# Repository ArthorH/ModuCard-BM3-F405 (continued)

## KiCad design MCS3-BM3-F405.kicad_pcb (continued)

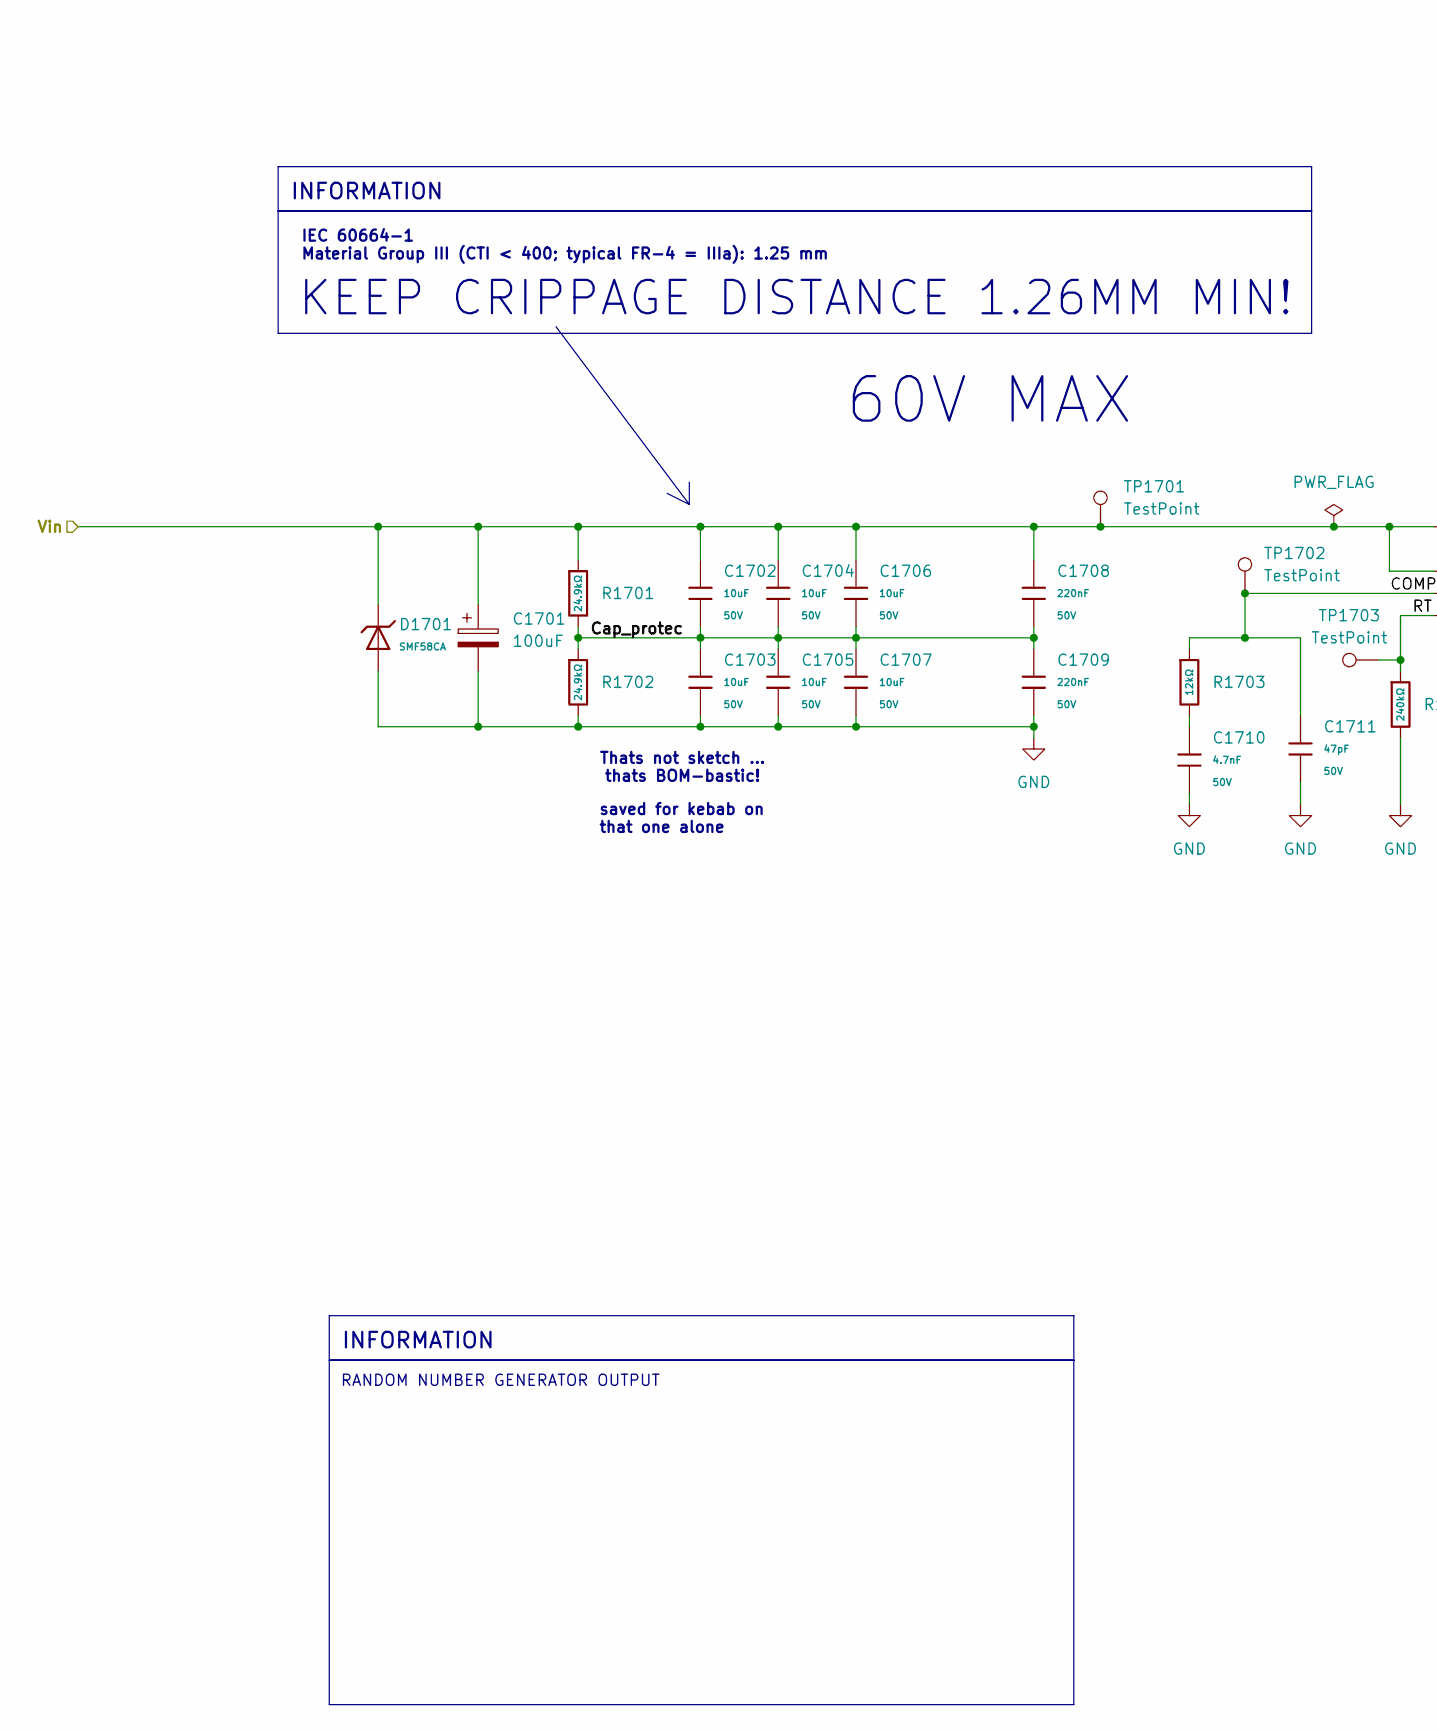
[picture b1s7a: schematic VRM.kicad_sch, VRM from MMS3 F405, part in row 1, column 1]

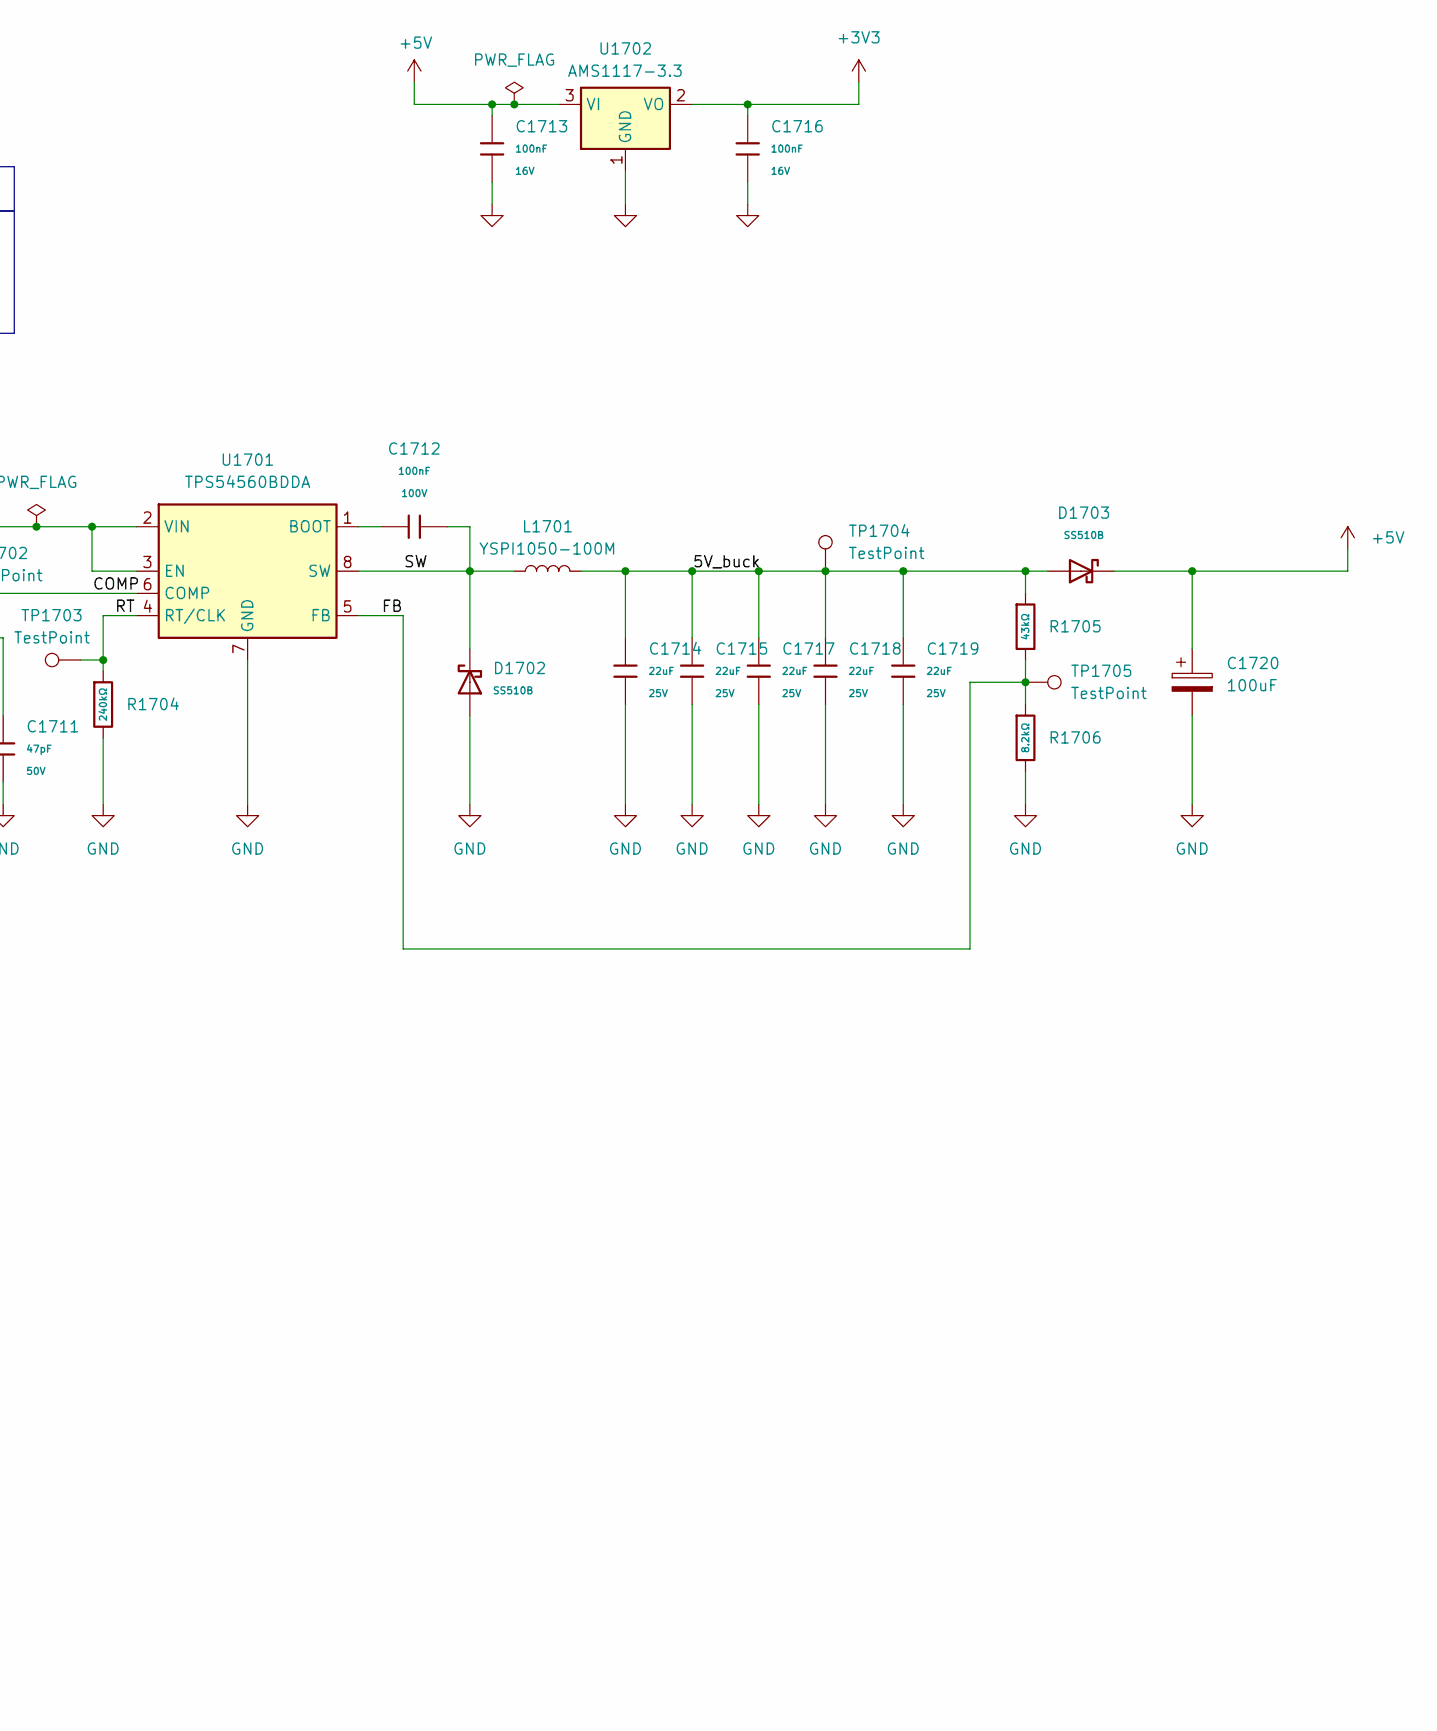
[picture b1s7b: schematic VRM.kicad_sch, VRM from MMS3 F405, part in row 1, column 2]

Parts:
C1701, C1720: 100uF; CP_Elec_10x10; MPN VZH101M1KTR-1010; LCSC C249838
C1702, C1703, C1704, C1705, C1706, C1707: 10uF; C_0805; Voltage Rated 50V; Tolerance ±10%; Part GRM21BR61H106KE43L; LCSC C440198
C1708, C1709: 220nF; C_0805; Voltage Rated 50V; Tolerance ±10%; Part CL21B224KBFNNNE; LCSC C5378
C1710: 4.7nF; C_0402; Voltage Rated 50V; Tolerance ±10%; Part 0402B472K500NT; LCSC C1538
C1711: 47pF; C_0402; Voltage Rated 50V; Tolerance ±5%; Part 0402CG470J500NT; LCSC C1567
C1712: 100nF; C_0805; Voltage Rated 100V; Tolerance ±10%; Part CL21B104KCFNNNE; LCSC C28233
C1713, C1716: 100nF; C_0402; Voltage Rated 16V; Tolerance ±10%; Part CL05B104KO5NNNC; LCSC C1525
C1714, C1715, C1717, C1718, C1719: 22uF; C_0805; Voltage Rated 25V; Tolerance ±20%; Part CL21A226MAQNNNE; LCSC C45783
D1701: SMF58CA; D_SOD-123FL; Clamping Voltage 93.6V; Voltage - Breakdown 71.2V; Part SMF58CA; LCSC C42371753
D1702, D1703: SS510B; D_SMB; Forward Voltage (Vf@If) 0.85V@5.0A; Reverse Voltage (Vr) 100V; Part SS510B; LCSC C7420368
L1701: YSPI1050-100M; L_Sunlord_MWSA1005S; LCSC C497897
R1701, R1702: 24.9kΩ; R_0402; Overload Voltage (Max) 50V; Tolerance ±1%; Part 0402WGF2402TCE; LCSC C25874
R1703: 12kΩ; R_0402; Overload Voltage (Max) 50V; Tolerance ±1%; Part 0402WGF1202TCE; LCSC C25752
R1704: 240kΩ; R_0603; Overload Voltage (Max) 75V; Tolerance ±1%; Part 0603WAF2403T5E; LCSC C4197
R1705: 43kΩ; R_0603; Overload Voltage (Max) 75V; Tolerance ±1%; Part 0603WAF4302T5E; LCSC C23172
R1706: 8.2kΩ; R_0402; Overload Voltage (Max) 50V; Tolerance ±1%; Part 0402WGF8201TCE; LCSC C25924
TP1701, TP1702, TP1703, TP1704, TP1705: TestPoint; TestPoint_Pad_D1.0mm
U1701: TPS54560BDDA; Texas_R-PDSO-G8_EP2.95x4.9mm_Mask2.4x3.1mm_ThermalVias
U1702: AMS1117-3.3; SOT-223-3_TabPin2

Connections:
+3V3: C1716.1, U1702.2 (VO); also elsewhere on the board
+5V: C1713.1, C1720.1, D1703.1, U1702.3 (VI); also elsewhere on the board
/VRM/5V_buck: C1714.1, C1715.1, C1717.1, C1718.1, C1719.1, D1703.2, L1701.2, R1705.1, TP1704.1 (1_1)
/VRM/COMP: C1711.1, R1703.1, TP1702.1 (1_1), U1701.6 (COMP)
/VRM/Cap_protec: C1702.2, C1703.1, C1704.2, C1705.1, C1706.2, C1707.1, C1708.2, C1709.1, R1701.2, R1702.1
/VRM/FB: R1705.2, R1706.1, TP1705.1 (1_1), U1701.5 (FB)
/VRM/RT: R1704.1, TP1703.1 (1_1), U1701.4 (RT/CLK)
/VRM/SW: C1712.1, D1702.1, L1701.1, U1701.8 (SW)
GND: C1701.2, C1703.2, C1705.2, C1707.2, C1709.2, C1710.2, C1711.2, C1713.2, C1714.2, C1715.2, C1716.2, C1717.2, C1718.2, C1719.2, C1720.2, D1701.2, D1702.2, R1702.2, R1704.2, R1706.2, U1701.7 (GND), U1701.9 (GND), U1702.1 (GND); also elsewhere on the board
unnamed: C1710.1, R1703.2
unnamed: C1712.2, U1701.1 (BOOT)
Vbat: C1701.1, C1702.1, C1704.1, C1706.1, C1708.1, D1701.1, R1701.1, TP1701.1 (1_1), U1701.2 (VIN), U1701.3 (EN); also elsewhere on the board

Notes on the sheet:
saved for kebab on that one alone
INFORMATION
KEEP CRIPPAGE DISTANCE 1.26MM MIN!
Thats not sketch ... thats BOM-bastic!
RANDOM NUMBER GENERATOR OUTPUT
60V MAX
IEC 60664-1 Material Group III (CTI < 400; typical FR-4 = IIIa): 1.25 mm

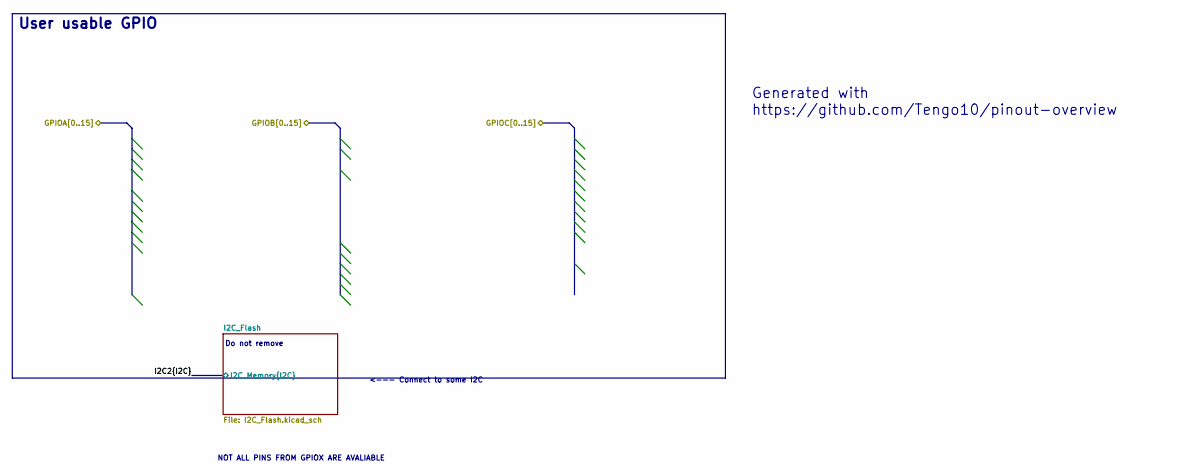
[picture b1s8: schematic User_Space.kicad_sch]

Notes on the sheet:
Do not remove
Generated with https://github.com/Tengo10/pinout-overview
<--- Connect to some I2C
User usable GPIO
NOT ALL PINS FROM GPIOX ARE AVALIABLE

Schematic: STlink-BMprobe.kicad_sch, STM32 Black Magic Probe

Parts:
C901, C905, C906, C907, C908, C909: 100nF; C_0402; Voltage Rated 50V; Tolerance ±10%; Part CL05B104KB54PNC; LCSC C307331
C902, C904: 33pF; C_0402; Voltage Rated 50V; Tolerance ±5%; Part 0402CG330J500NT; LCSC C1562
C903: 1uF; C_0402; Voltage Rated 25V; Tolerance ±10%; Part CL05A105KA5NQNC; LCSC C52923
D901, D902: Red; D_0603; Part KT-0603R; LCSC C2286
J901: Conn_02x02_Counter_Clockwise; PinSocket_2x02_P2.54mm_Vertical; not fitted
Q901: MMST3904; SOT-23; Part MMST3904; LCSC C20526
R901, R904: 100kΩ; R_0402; Overload Voltage (Max) 50V; Tolerance ±1%; Part 0402WGF1003TCE; LCSC C25741
R902, R903, R908, R909: 22Ω; R_0402; Overload Voltage (Max) 50V; Tolerance ±1%; Part 0402WGF220JTCE; LCSC C25092
R905, R917: 100Ω; R_0402; Overload Voltage (Max) 50V; Tolerance ±1%; Part 0402WGF1000TCE; LCSC C25076
R906, R912, R913, R915: 10kΩ; R_0402; Overload Voltage (Max) 50V; Tolerance ±1%; Part 0402WGF1002TCE; LCSC C25744
R907: 10kΩ; R_0402; Overload Voltage (Max) 50V; Tolerance ±1%; Part 0402WGF1002TCE; LCSC C25744; not fitted
R910, R911: 220Ω; R_0402; Overload Voltage (Max) 50V; Tolerance ±1%; Part 0402WGF2200TCE; LCSC C25091
R914: 1.5kΩ; R_0402; Overload Voltage (Max) 50V; Tolerance ±1%; Part 0402WGF1501TCE; LCSC C25867
R916: 24.9kΩ; R_0402; Overload Voltage (Max) 50V; Tolerance ±1%; Part 0402WGF2402TCE; LCSC C25874
TP901, TP902, TP903, TP904, TP905, TP906, TP907, TP908: TestPoint; TestPoint_Pad_D1.0mm
U901: STM32F103CBTx; LQFP-48_7x7mm_P0.5mm; LCSC C8304
Y901: Crystal_GND24; CRYSTAL-SMD_4P-L3.2-W2.5-BL; MPN 3225-8.00-20-10-10/4B; LCSC C7424755

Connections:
+3V3: C903.1, C905.1, C906.1, C907.1, C908.1, C909.1, J901.2, Q901.3 (C), R901.1, R910.1, R912.1, U901.1 (VBAT), U901.9 (VDDA), U901.24 (VDD), U901.36 (VDD), U901.48 (VDD); also elsewhere on the board
+5V: R915.1; also elsewhere on the board
/MCU/Debug_Uart.RX: U901.12 (PA2); also elsewhere on the board
/MCU/Debug_Uart.TX: U901.13 (PA3); also elsewhere on the board
/MCU/SWD.SWCLK: R902.1, R909.2, TP904.1; also elsewhere on the board
/MCU/SWD.SWDIO: R903.1, TP903.1; also elsewhere on the board
/MCU/SWD.~RST: R908.1, TP905.1; also elsewhere on the board
/STlink-BMprobe/CLK: J901.4, U901.37 (PA14)
/STlink-BMprobe/DIO: J901.3, U901.34 (PA13)
/STlink-BMprobe/LED: D901.1, D902.2, U901.30 (PA9)
/STlink-BMprobe/ST-LINK.D+: R914.2, TP902.1, U901.33 (PA12); also elsewhere on the board
/STlink-BMprobe/ST-LINK.D-: TP901.1, U901.32 (PA11); also elsewhere on the board
/STlink-BMprobe/STLINK-BOOT0: R904.2, TP907.1 (1_1), U901.44 (BOOT0)
/STlink-BMprobe/STLINK-OSC_IN: C902.1, U901.5 (PD0), Y901.1
/STlink-BMprobe/STLINK-OSC_OUT: C904.1, U901.6 (PD1), Y901.3
/STlink-BMprobe/STLINK-RST: C901.1, R901.2, TP908.1 (1_1), U901.7 (NRST)
/STlink-BMprobe/SWO: U901.31 (PA10)
/STlink-BMprobe/USB_RENUM: R917.2, TP906.1, U901.38 (PA15)
GND: C901.2, C902.2, C903.2, C904.2, C905.2, C906.2, C907.2, C908.2, C909.2, J901.1, R904.1, R906.1, R907.1, R911.2, R913.2, R916.2, U901.8 (VSSA), U901.23 (VSS), U901.35 (VSS), U901.47 (VSS), Y901.2, Y901.4; also elsewhere on the board
unnamed: D901.2, R910.2
unnamed: D902.1, R911.1
unnamed: Q901.1 (B), R915.2, R916.1, R917.1
unnamed: Q901.2 (E), R914.1
unnamed: R912.2, R913.1, U901.10 (PA0)
unnamed: R909.1, U901.15 (PA5)
unnamed: R908.2, U901.18 (PB0)
unnamed: R905.2, U901.25 (PB12)
unnamed: R902.2, U901.26 (PB13)
unnamed: R903.2, R905.1, U901.27 (PB14)
unnamed: R906.2, U901.2 (PC13)
unnamed: R907.2, U901.3 (PC14)

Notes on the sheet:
https://github.com/lbthomsen/st-link/tree/master
NOTE:
Flashing pins for BM Probe
Monitor voltage rail 3V3 instead of target MCU voltage
Should be 1k5, but we try 1k2 because it is in basic parts
NOTICE:
CAUTION:
Alternative GD32F103CB
Populate with STM32F103C8, STM32F103CB
MANDATORY CB VERSION
ACTIVITY LED
for providing amazing reverse engeenering of ST-link
C707=C708 = (CL - 4pF) * 2
Credit to:
https://stm32world.com/wiki/DIY_STM32_Programmer_(ST-Link/V2-1)
UART FLIP HERE
ALTERNATE PART: GigaDevice Semicon Beijing GD32F103CBT6 PIN AND FW COMPATIBLE WAZZUP BEIJING
FORCE RENUMERATION OF USB DEVICES

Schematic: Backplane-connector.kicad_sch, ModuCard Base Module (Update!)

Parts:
J501: 09031967921; DIN41612_C_3x32_Male_Horizontal_THT; PARTREV D

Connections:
/Backplane-connector/CAN1.+: J501.a30 (a3), J501.c30 (c3); also elsewhere on the board
/Backplane-connector/CAN1.-: J501.a29 (a4), J501.c29 (c4); also elsewhere on the board
/Backplane-connector/CAN2.+: J501.a28 (a5), J501.c28 (c5); also elsewhere on the board
/Backplane-connector/CAN2.-: J501.a27 (a6), J501.c27 (c6); also elsewhere on the board
/Backplane-connector/GPIOL1: J501.c26 (c7)
/Backplane-connector/GPIOL2: J501.c25 (c8)
/Backplane-connector/GPIOL3: J501.c24 (c9)
/Backplane-connector/GPIOL4: J501.c23 (c10)
/Backplane-connector/GPIOL5: J501.c22 (c11)
/Backplane-connector/GPIOL6: J501.c21 (c12)
/Backplane-connector/GPIOL7: J501.c20 (c13)
/Backplane-connector/GPIOL8: J501.c19 (c14)
/Backplane-connector/GPIOL9: J501.c18 (c15)
/Backplane-connector/GPIOL10: J501.c17 (c16)
/Backplane-connector/GPIOL11: J501.c16 (c17)
/Backplane-connector/GPIOL12: J501.c15 (c18)
/Backplane-connector/GPIOL13: J501.c14 (c19)
/Backplane-connector/GPIOL14: J501.c13 (c20)
/Backplane-connector/GPIOL15: J501.c12 (c21)
/Backplane-connector/GPIOL16: J501.c11 (c22)
/Backplane-connector/GPIOR1: J501.a26 (a7)
/Backplane-connector/GPIOR2: J501.a25 (a8)
/Backplane-connector/GPIOR3: J501.a24 (a9)
/Backplane-connector/GPIOR4: J501.a23 (a10)
/Backplane-connector/GPIOR5: J501.a22 (a11)
/Backplane-connector/GPIOR6: J501.a21 (a12)
/Backplane-connector/GPIOR7: J501.a20 (a13)
/Backplane-connector/GPIOR8: J501.a19 (a14)
/Backplane-connector/GPIOR9: J501.a18 (a15)
/Backplane-connector/GPIOR10: J501.a17 (a16)
/Backplane-connector/GPIOR11: J501.a16 (a17)
/Backplane-connector/GPIOR12: J501.a15 (a18)
/Backplane-connector/GPIOR13: J501.a14 (a19)
/Backplane-connector/GPIOR14: J501.a13 (a20)
/Backplane-connector/GPIOR15: J501.a12 (a21)
/Backplane-connector/GPIOR16: J501.a11 (a22)
/Backplane-connector/Index_1: J501.b32 (b1); also elsewhere on the board
/Backplane-connector/Index_2: J501.b31 (b2); also elsewhere on the board
/Backplane-connector/Strobe1.+: J501.b30 (b3); also elsewhere on the board
/Backplane-connector/Strobe1.-: J501.b29 (b4); also elsewhere on the board
/Backplane-connector/Strobe2.+: J501.b28 (b5); also elsewhere on the board
/Backplane-connector/Strobe2.-: J501.b27 (b6); also elsewhere on the board
/Backplane-connector/USB.D+: J501.a31 (a2); also elsewhere on the board
/Backplane-connector/USB.D-: J501.c31 (c2); also elsewhere on the board
GND: J501.a1 (a32), J501.a10 (a23), J501.a32 (a1), J501.b1 (b32), J501.b10 (b23), J501.b11 (b22), J501.b12 (b21), J501.b13 (b20), J501.b14 (b19), J501.b15 (b18), J501.b16 (b17), J501.b17 (b16), J501.b18 (b15), J501.b19 (b14), J501.b20 (b13), J501.b21 (b12), J501.b22 (b11), J501.b23 (b10), J501.b24 (b9), J501.b25 (b8), J501.b26 (b7), J501.c1 (c32), J501.c10 (c23), J501.c32 (c1); also elsewhere on the board
Vbat: J501.a2 (a31), J501.a3 (a30), J501.a4 (a29), J501.a5 (a28), J501.a6 (a27), J501.a7 (a26), J501.a8 (a25), J501.a9 (a24), J501.b2 (b31), J501.b3 (b30), J501.b4 (b29), J501.b5 (b28), J501.b6 (b27), J501.b7 (b26), J501.b8 (b25), J501.b9 (b24), J501.c2 (c31), J501.c3 (c30), J501.c4 (c29), J501.c5 (c28), J501.c6 (c27), J501.c7 (c26), J501.c8 (c25), J501.c9 (c24); also elsewhere on the board

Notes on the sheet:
USB
CAN1
CAN2

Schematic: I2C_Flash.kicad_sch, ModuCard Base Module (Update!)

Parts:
C101: 100nF; C_0402; Voltage Rated 50V; Tolerance ±10%; Part CL05B104KB54PNC; LCSC C307331
R101, R102, R104, R106: 10kΩ; R_0402; Overload Voltage (Max) 50V; Tolerance ±1%; Part 0402WGF1002TCE; LCSC C25744
R103, R105, R107: 10kΩ; R_0402; Overload Voltage (Max) 50V; Tolerance ±1%; Part 0402WGF1002TCE; LCSC C25744; not fitted
U101: AT24C256C; SOIC-8_5.3x5.3mm_P1.27mm; Supply Voltage 1.7V~5.5V; Part AT24C256C-SSHL-T; LCSC C6482

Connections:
+3V3: C101.1, R102.1, R104.1, R106.1, U101.8 (VCC); also elsewhere on the board
/User Space/I2C2.SCL: U101.6 (SCL)
/User Space/I2C2.SDA: U101.5 (SDA)
/User Space/I2C_Flash/A0: R106.2, R107.1, U101.1 (A0)
/User Space/I2C_Flash/A1: R104.2, R105.1, U101.2 (A1)
/User Space/I2C_Flash/A2: R102.2, R103.1, U101.3 (A2)
GND: C101.2, R101.2, R103.2, R105.2, R107.2, U101.4 (GND); also elsewhere on the board
unnamed: R101.1, U101.7 (WP)

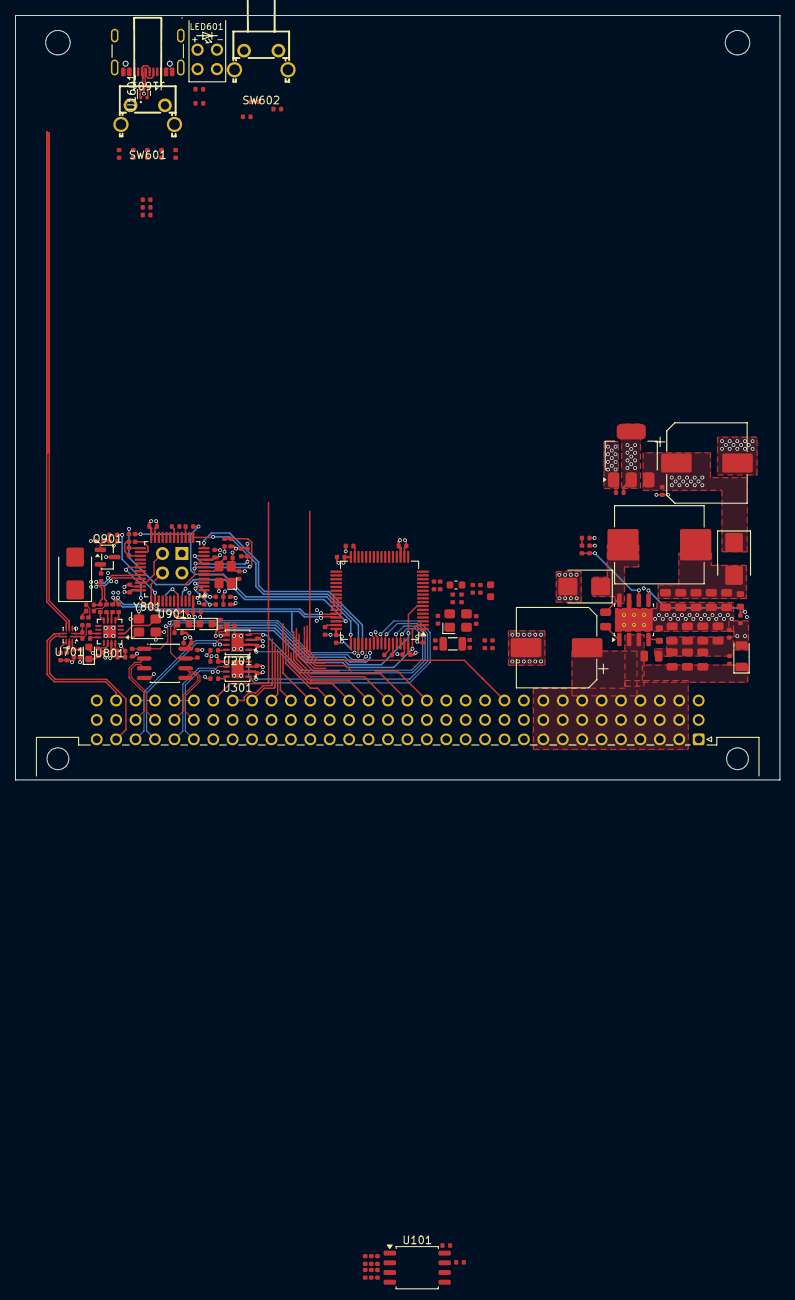
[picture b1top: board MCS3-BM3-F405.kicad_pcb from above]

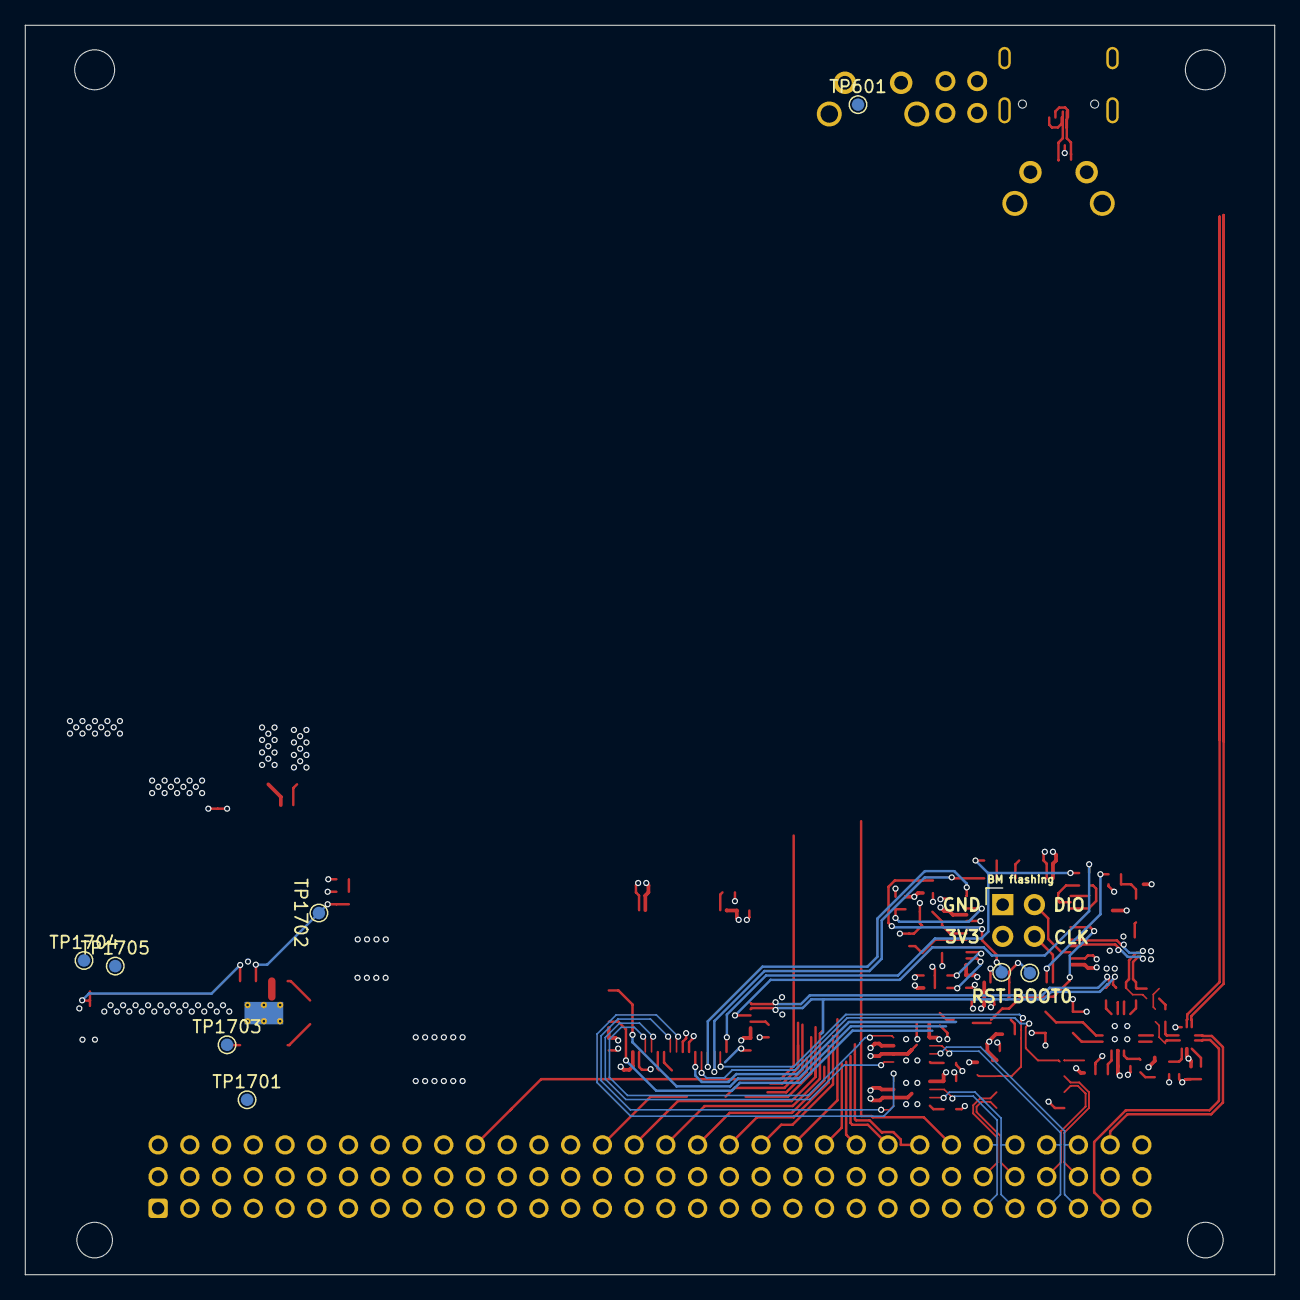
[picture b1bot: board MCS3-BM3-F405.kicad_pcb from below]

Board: 4 copper layers, 100.0 x 100.0 mm, 178 parts (9 on the bottom side), 104 nets.

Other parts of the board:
kibuzzard-67B20BD5: G***; kibuzzard-67B20BD5
kibuzzard-67B63E8D: G***; kibuzzard-67B63E8D
kibuzzard-67B219C6: G***; kibuzzard-67B219C6
kibuzzard-67B624A4: G***; kibuzzard-67B624A4
kibuzzard-67B643AC: G***; kibuzzard-67B643AC
kibuzzard-67B643DE: G***; kibuzzard-67B643DE
kibuzzard-67B643EE: G***; kibuzzard-67B643EE
kibuzzard-67B2198C: G***; kibuzzard-67B2198C
kibuzzard-67B6248A: G***; kibuzzard-67B6248A
kibuzzard-67B6249A: G***; kibuzzard-67B6249A
kibuzzard-67B6438D: G***; kibuzzard-67B6438D
kibuzzard-67B37005: G***; kibuzzard-67B37005
kibuzzard-67B37418: G***; kibuzzard-67B37418
kibuzzard-67B37472: G***; kibuzzard-67B37472
kibuzzard-67B62451: G***; kibuzzard-67B62451
kibuzzard-67B62470: G***; kibuzzard-67B62470
kibuzzard-67BE3F52: G***; kibuzzard-67BE3F52
kibuzzard-67E7D86B: G***; kibuzzard-67E7D86B

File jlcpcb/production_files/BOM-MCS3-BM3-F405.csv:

Comment,Designator,Footprint,LCSC,Quantity
1.5kΩ,R914,R_0402,C25867,1
100kΩ,"R901,R904",R_0402,C25741,2
100nF,"C1713,C1716,C610",C_0402,C1525,3
100nF,C1712,C_0805,C28233,1
100nF,"C101,C1602,C201,C202,C301,C302,C602,C603,C604,C605,C606,C608,C609,C613,C617,C621,C701,C801,C901,C905,C906,C907,C908,C909",C_0402,C307331,24
100uF,"C1701,C1720",CP_Elec_10x10,C249838,2
100Ω,"R604,R605,R609,R905,R917",R_0402,C25076,5
10kΩ,"R101,R102,R104,R106,R201,R301,R601,R602,R608,R610,R611,R701,R703,R906,R912,R913,R915",R_0402,C25744,17
10nF,C1601,C_0402,C15195,1
10uF,"C615,C620,C802",C_0402,C15525,3
10uF,C601,C_0603,C19702,1
10uF,"C1702,C1703,C1704,C1705,C1706,C1707",C_0805,C440198,6
12kΩ,R1703,R_0402,C25752,1
18pF,"C616,C618",C_0402,C1549,2
1kΩ,"R606,R607,R809",R_0402,C11702,3
1uF,"C803,C903",C_0402,C52923,2
2.2uF,"C611,C612",C_0402,C12530,2
220nF,"C1708,C1709",C_0805,C5378,2
220Ω,"R910,R911",R_0402,C25091,2
22kΩ,R702,R_0402,C25768,1
22pF,"C614,C619",C_0402,C1555,2
22uF,"C1714,C1715,C1717,C1718,C1719",C_0805,C45783,5
22Ω,"R801,R802,R805,R806,R807,R808,R902,R903,R908,R909",R_0402,C25092,10
24.9kΩ,"R1701,R1702,R916",R_0402,C25874,3
240kΩ,R1704,R_0603,C4197,1
33kΩ,R1601,R_0402,C25779,1
33pF,"C902,C904",C_0402,C1562,2
4.7nF,C1710,C_0402,C1538,1
43kΩ,R1705,R_0603,C23172,1
47pF,C1711,C_0402,C1567,1
5.1kΩ,"R1602,R1603",R_0402,C25905,2
8.2kΩ,R1706,R_0402,C25924,1
AT24C256C,U101,SOIC-8_5.3x5.3mm_P1.27mm,C6482,1
Crystal_GND24,Y901,CRYSTAL-SMD_4P-L3.2-W2.5-BL,C7424755,1
Crystal_GND24,Y801,Crystal_SMD_3225-4Pin_3.2x2.5mm,C9002,1
FSUSB42UMX,U701,UQFN-10_1.4x1.8mm_P0.4mm,C11145,1
LM358DR2G,U603,SOIC-8_L5.0-W4.0-P1.27-LS6.0-BL,C7950,1
MMST3904,Q901,SOT-23,C20526,1
Q13FC1350000400,X602,FC-135R_L3.2-W1.5,C97606,1
Red,"D801,D901,D902",D_0603,C2286,3
SMF58CA,D1701,D_SOD-123FL,C42371753,1
SS510B,"D101,D1702,D1703",D_SMB,C7420368,3
STM32F103CBTx,U901,LQFP-48_7x7mm_P0.5mm,C8304,1
STM32F405RGTx,U601,LQFP-64_10x10mm_P0.5mm,C15742,1
TC-6615Z-12.5-260,"SW601,SW602",SW-TH_4P-L7.3-TC-6615Z-12.5-260,C7528758,2
TJA1044GTK_3Z,"U201,U301",HVSON-8-1EP_3x3mm_P0.65mm_EP1.6x2.4mm,C5215851,2
TPD2EUSB30DRTR-TP,U1601,SOT-723,C2844720,1
USB_C_Receptacle_USB2.0_16P,J1601,USB_C_Receptacle_GCT_USB4105-xx-A_16P_TopMnt_Horizontal,C165948,1
X32258MOB4SI,X601,OSC-SMD_4P-L3.2-W2.5-BL,C2682775,1
YSPI1050-100M,L1701,L_Sunlord_MWSA1005S,C497897,1
~,FB601,FB_0603,C1002,1
09031967921,J501,DIN41612_C_3x32_Male_Horizontal_THT,,1
CH334P,U801,QFN-16-1EP_3x3mm_P0.5mm_EP1.7x1.7mm,,1
TPS54560BDDA,U1701,Texas_R-PDSO-G8_EP2.95x4.9mm_Mask2.4x3.1mm_ThermalVias,,1
FixLed307,LED601,FixLed307,,1
AMS1117-3.3,U1702,SOT-223-3_TabPin2,,1
TestPoint,TP601,TestPoint_Pad_D1.0mm,,1
TestPoint,TP1705,TestPoint_Pad_D1.0mm,,1
TestPoint,TP907,TestPoint_Pad_D1.0mm,,1
TestPoint,TP1701,TestPoint_Pad_D1.0mm,,1
TestPoint,TP1703,TestPoint_Pad_D1.0mm,,1
TestPoint,TP1702,TestPoint_Pad_D1.0mm,,1
TestPoint,TP1704,TestPoint_Pad_D1.0mm,,1
TestPoint,TP908,TestPoint_Pad_D1.0mm,,1
